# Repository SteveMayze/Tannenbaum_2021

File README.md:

# Tannenbaum
 An sdvent project for an illuminated Christmas tree.

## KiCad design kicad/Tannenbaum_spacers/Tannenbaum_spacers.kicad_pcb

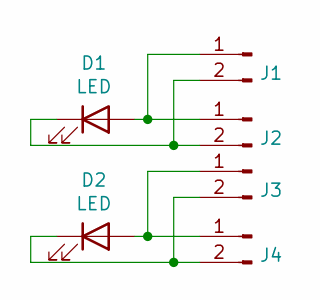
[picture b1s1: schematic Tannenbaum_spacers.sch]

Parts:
D1, D2: LED; LED_D5.0mm
J1, J2, J3, J4: Conn_01x02_Male; Pin_Header_Straight_1x02_Pitch2.00mm

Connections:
unnamed: D1.1 (K), J1.2, J2.2
unnamed: D1.2 (A), J1.1, J2.1
unnamed: D2.1 (K), J3.2, J4.2
unnamed: D2.2 (A), J3.1, J4.1

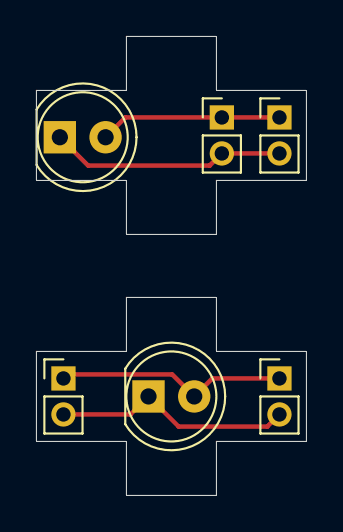
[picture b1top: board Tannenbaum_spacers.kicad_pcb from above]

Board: 2 copper layers, 15.0 x 25.5 mm, 6 parts (0 on the bottom side), 4 nets.

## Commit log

2021-11-21 Design #5. This is more stable and considers the power cable.
2021-11-21 Update to the power calculations and adds a Star Tray.
2021-11-23 Added support for the star
2021-11-25 Documentation photos
2021-11-26 Updated photos and costs
2021-11-27 Reduced the image size
2021-11-27 removed the large images
2021-12-02 Creates the images for the writeup.
2021-12-03 Creates the initial PCB version of the spacer
2021-12-12 Updates to the rev 6
